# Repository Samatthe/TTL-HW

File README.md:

# TTL-HW
Hardware for the TelTail Light's Control Module, an interactive lighting controller for DIY electric skateboards

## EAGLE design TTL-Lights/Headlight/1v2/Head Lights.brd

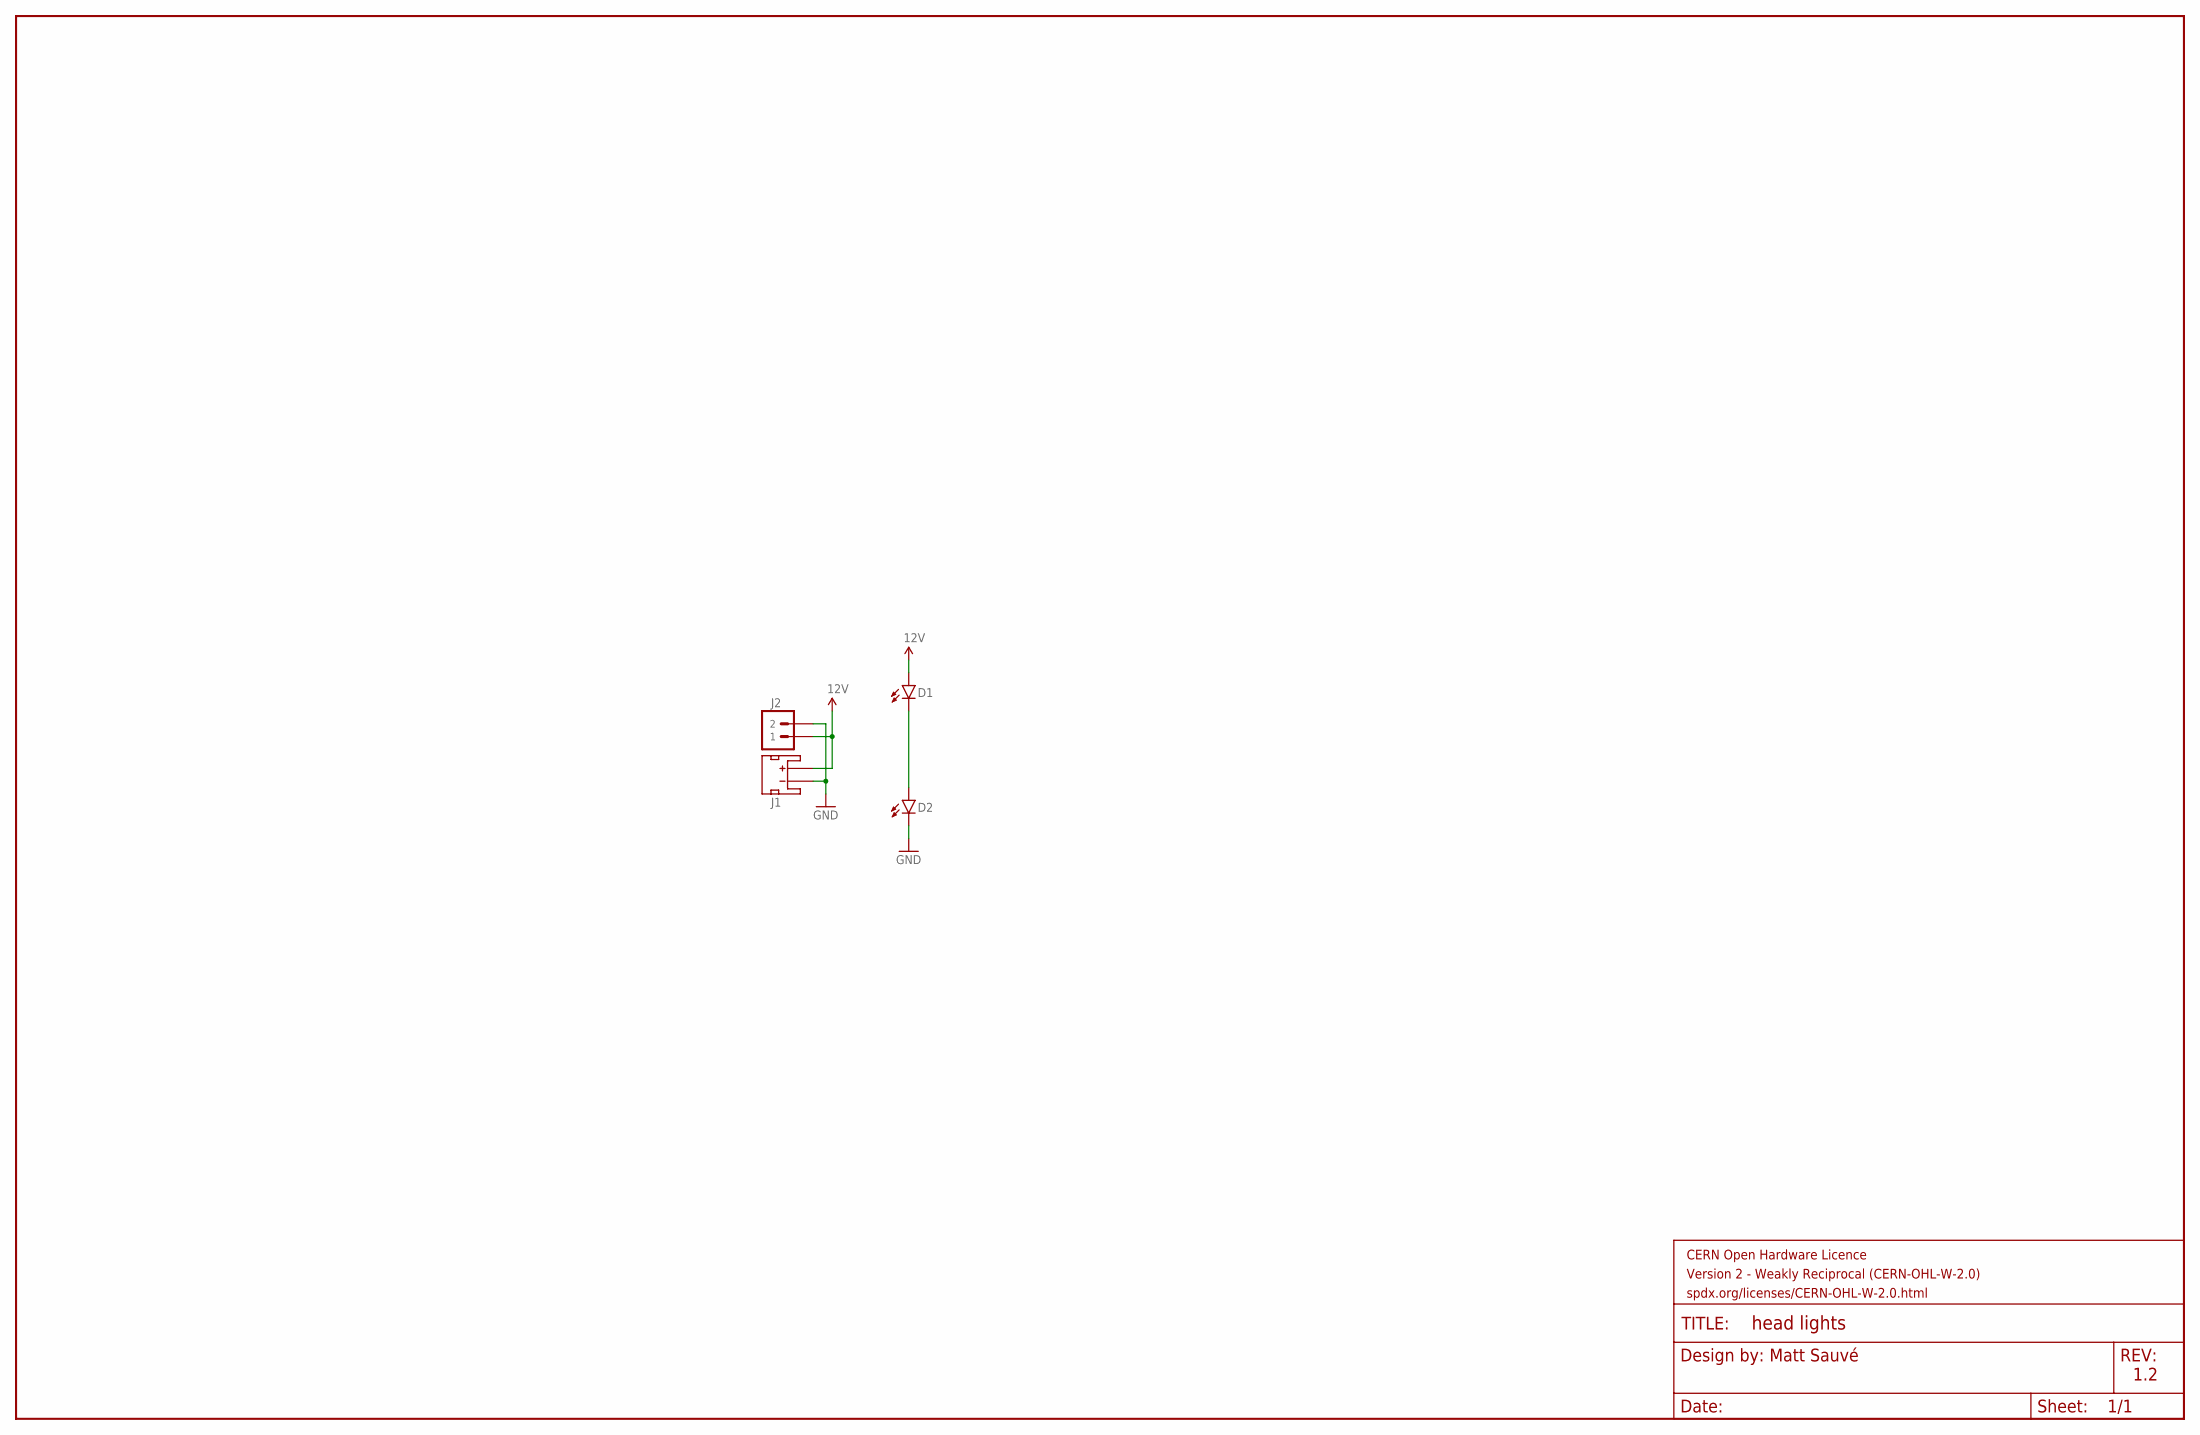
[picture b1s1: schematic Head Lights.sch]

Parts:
D1, D2: WHITE_LUXEON_LED; 1414
FRAME1: FRAME-LEDGER_CERN_WEAK; CERN_WEAK
J1: JST_2MM_MALE; JST-2-SMD
J2: JST_PH_2POS

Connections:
12V: D1.P$1 (A), J1.2 (+), J2.1
GND: D2.P$2 (C), J1.1 (-), J2.2
unnamed: D1.P$2 (C), D2.P$1 (A)

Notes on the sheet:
Matt Sauvé
1.2

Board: 2 copper layers, 5 parts (2 on the bottom side), 3 nets, no tracks yet.

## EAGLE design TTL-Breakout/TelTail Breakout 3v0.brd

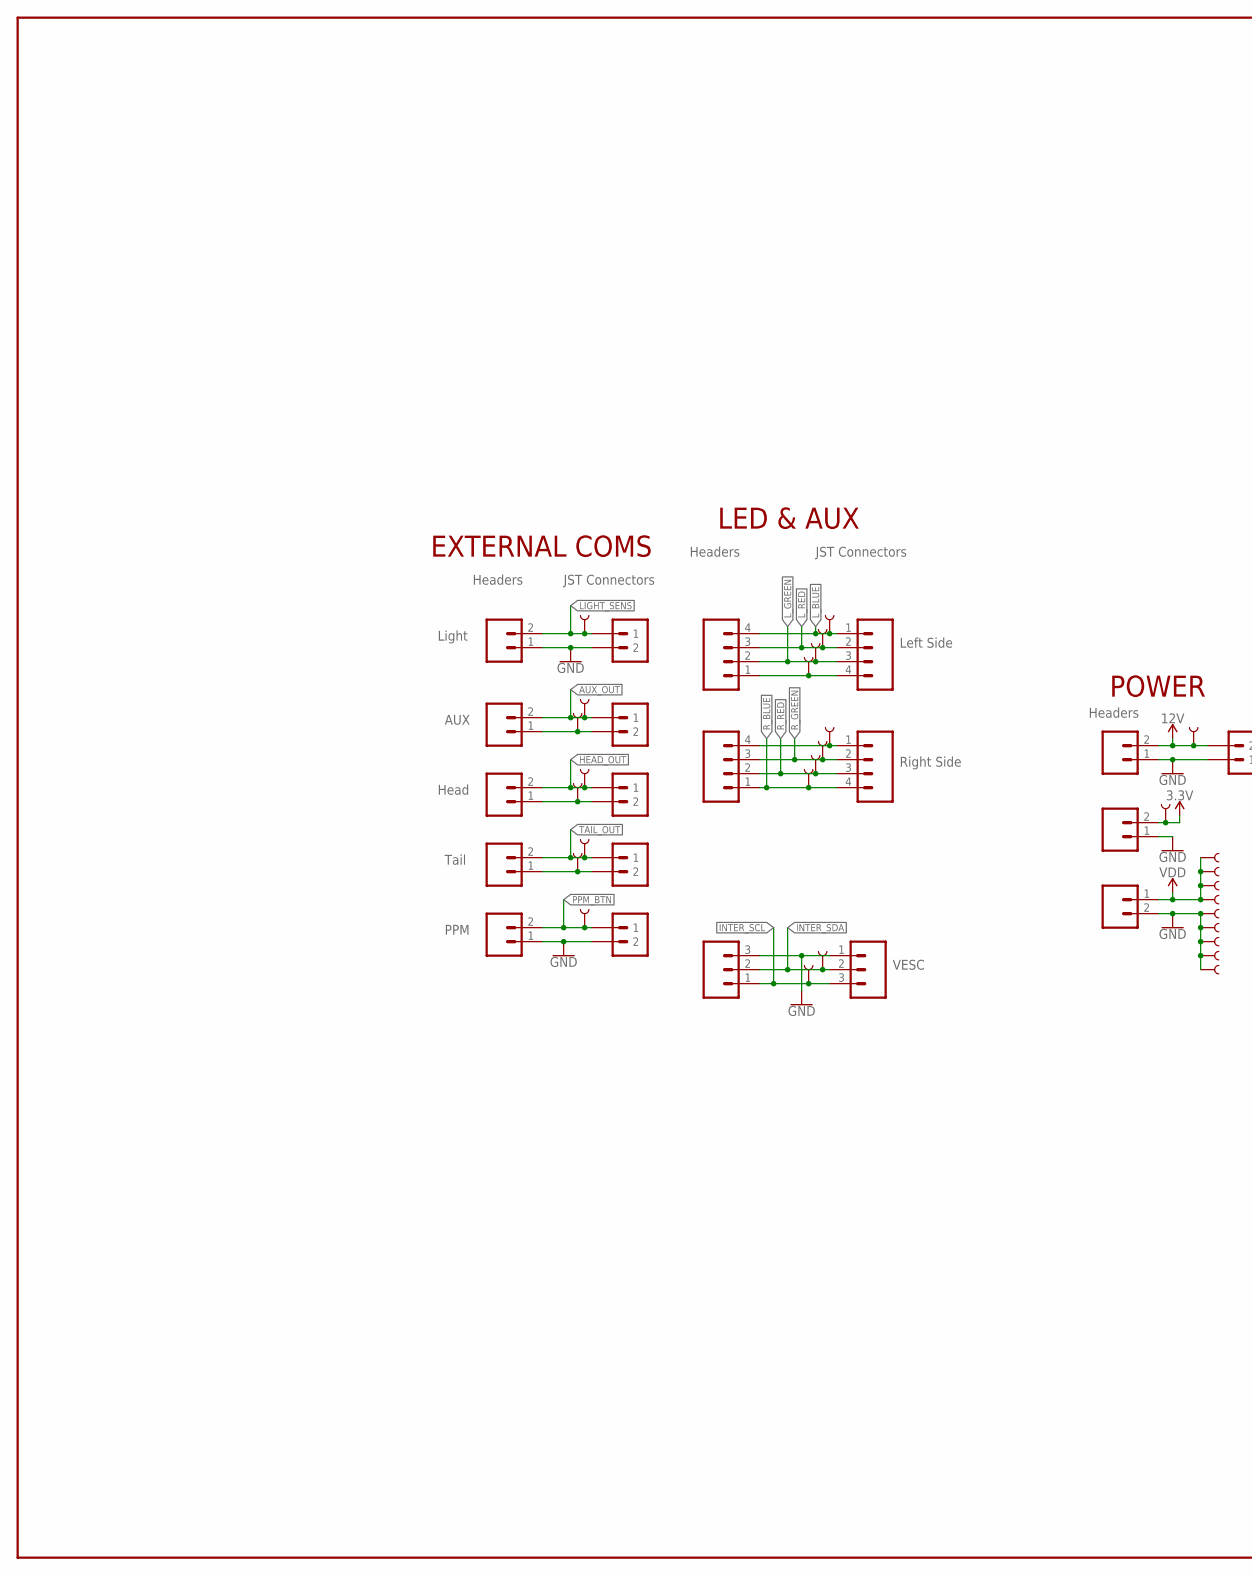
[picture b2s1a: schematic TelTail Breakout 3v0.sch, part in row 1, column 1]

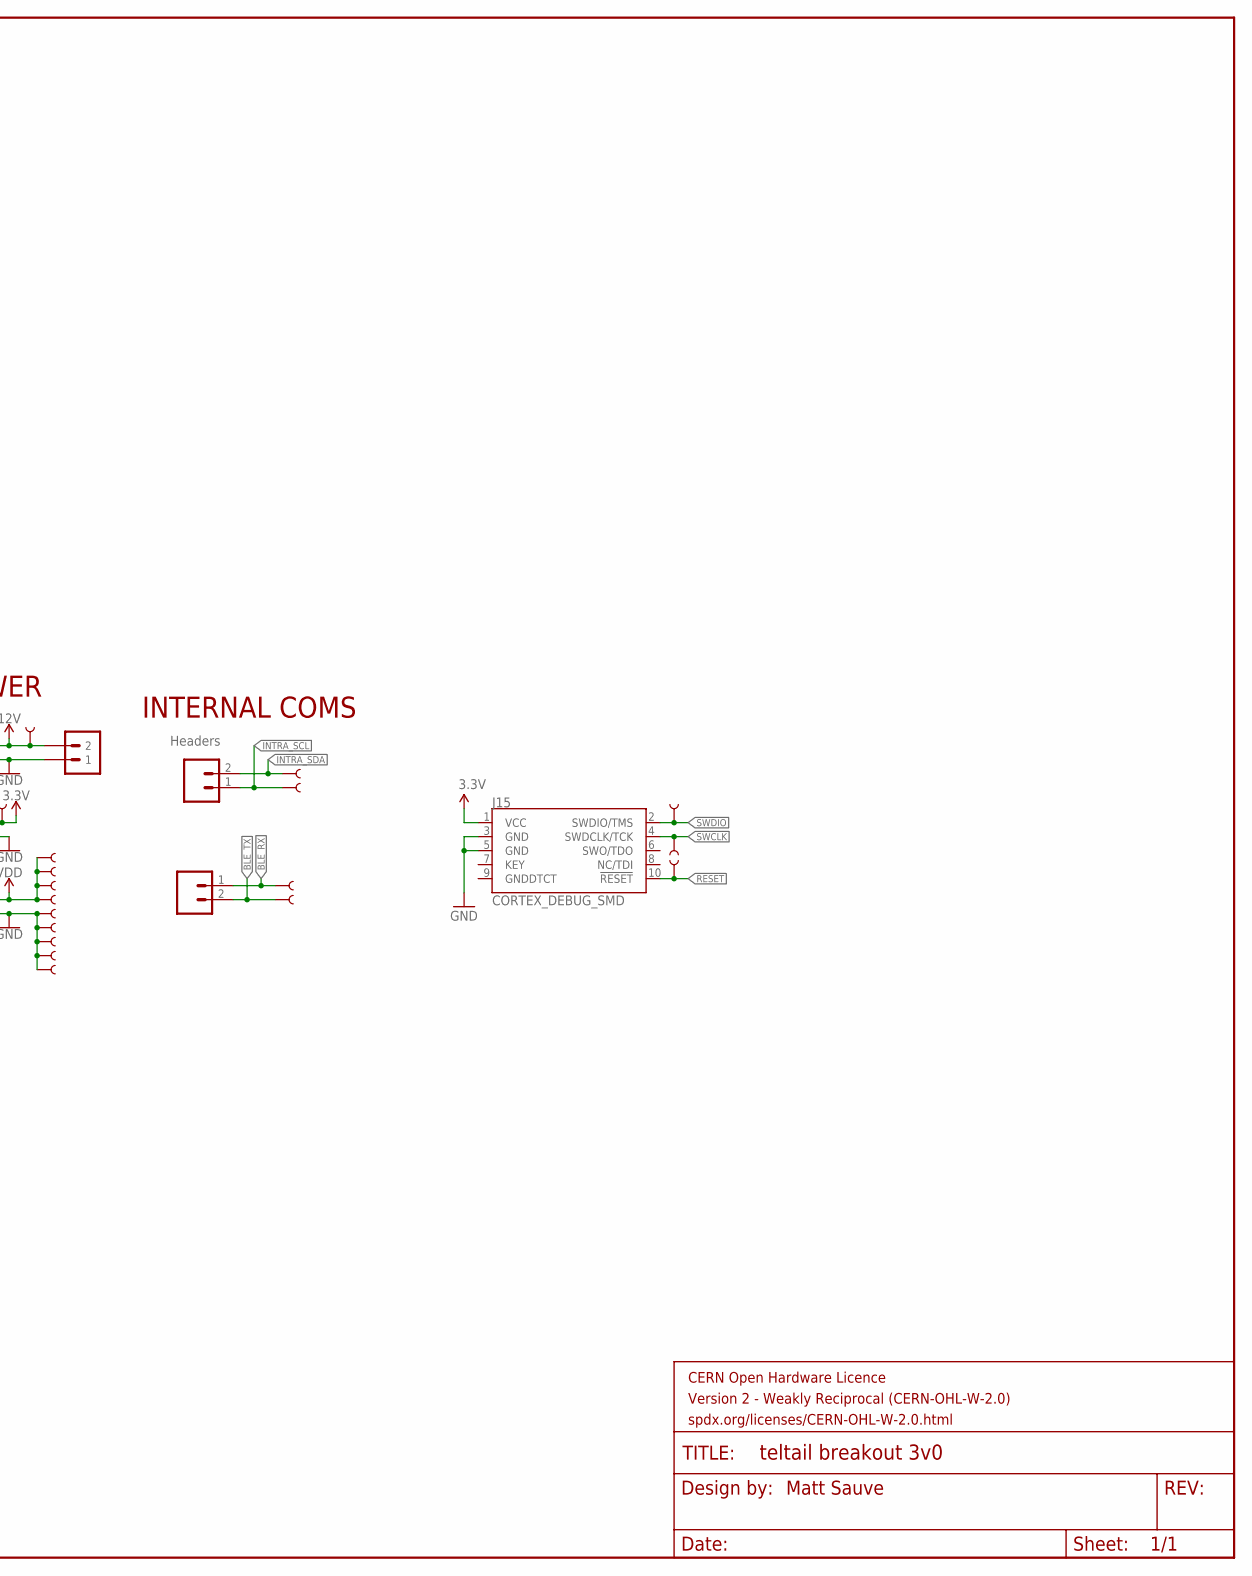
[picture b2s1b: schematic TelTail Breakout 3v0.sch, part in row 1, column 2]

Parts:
FRAME1: FRAME-LEDGER_CERN_WEAK; CERN_WEAK
J1, J2, J3, J4, J5, J6, J11, J12, J13, J14: CONN_02; 1X02
J7: CONN_03; 1X03
J9, J10: CONN_04; 1X04
J15: CORTEX_DEBUG_SMD; SAMTECH_FTSH-105-01
U$1, U$2, U$3, U$4, U$5, U$45: JST_PH_2POS
U$6, U$11, U$12, U$13, U$14, U$15, U$16, U$17, U$18, U$19, U$20, U$21, U$22, U$23, U$24, U$25, U$26, U$27, U$28, U$29, U$30, U$31, U$32, U$33, U$34, U$35, U$36, U$37, U$38, U$39, U$40, U$42, U$43, U$44, U$46, U$48: POGO_PIN_90173-AS
U$8, U$10: JST_PH_4POS
U$9: JST_PH_3POS

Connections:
3.3V: J12.2, J15.1 (VCC), U$20.P$1
12V: J11.2, U$38.P$1, U$45.2
!RESET: J15.10 (!RESET), U$36.P$1
AUX_OUT: J2.2, U$4.1, U$31.P$1
BLE_RX: J14.1, U$46.P$1
BLE_TX: J14.2, U$48.P$1
GND: J1.1, J5.1, J6.2, J7.3, J11.1, J12.1, J15.3 (GND), J15.5 (GND), U$1.2, U$5.2, U$6.P$1, U$9.1 (2), U$24.P$1, U$28.P$1, U$30.P$1, U$40.P$1, U$45.1
HEAD_OUT: J3.2, U$3.1, U$29.P$1
INTER_SCL: J7.1, U$9.3 (4), U$19.P$1
INTER_SDA: J7.2, U$9.2 (3), U$21.P$1
INTRA_SCL: J13.1, U$44.P$1
INTRA_SDA: J13.2, U$43.P$1
LIGHT_SENS: J1.2, U$5.1, U$33.P$1
L_BLUE: J10.4, U$10.1, U$11.P$1
L_GREEN: J10.2, U$10.3, U$13.P$1
L_RED: J10.3, U$10.2, U$12.P$1
unnamed: J4.1, U$2.2, U$35.P$1
unnamed: J3.1, U$3.2, U$34.P$1
unnamed: J2.1, U$4.2, U$32.P$1
unnamed: J10.1, U$10.4, U$14.P$1
unnamed: J9.4, U$8.1, U$15.P$1
PPM_BTN: J5.2, U$1.1, U$25.P$1
R_BLUE: J9.1, U$8.4, U$18.P$1
R_GREEN: J9.3, U$8.2, U$16.P$1
R_RED: J9.2, U$8.3, U$17.P$1
SWCLK: J15.4 (SWDCLK/TCK), U$37.P$1
SWDIO: J15.2 (SWDIO/TMS), U$39.P$1
TAIL_OUT: J4.2, U$2.1, U$27.P$1
VDD: J6.1, U$22.P$1, U$23.P$1, U$26.P$1, U$42.P$1

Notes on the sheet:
VESC
Right Side
Left Side
JST Connectors
Headers
Light
AUX
Head
Tail
PPM
POWER
LED & AUX
EXTERNAL COMS
INTERNAL COMS
Matt Sauve

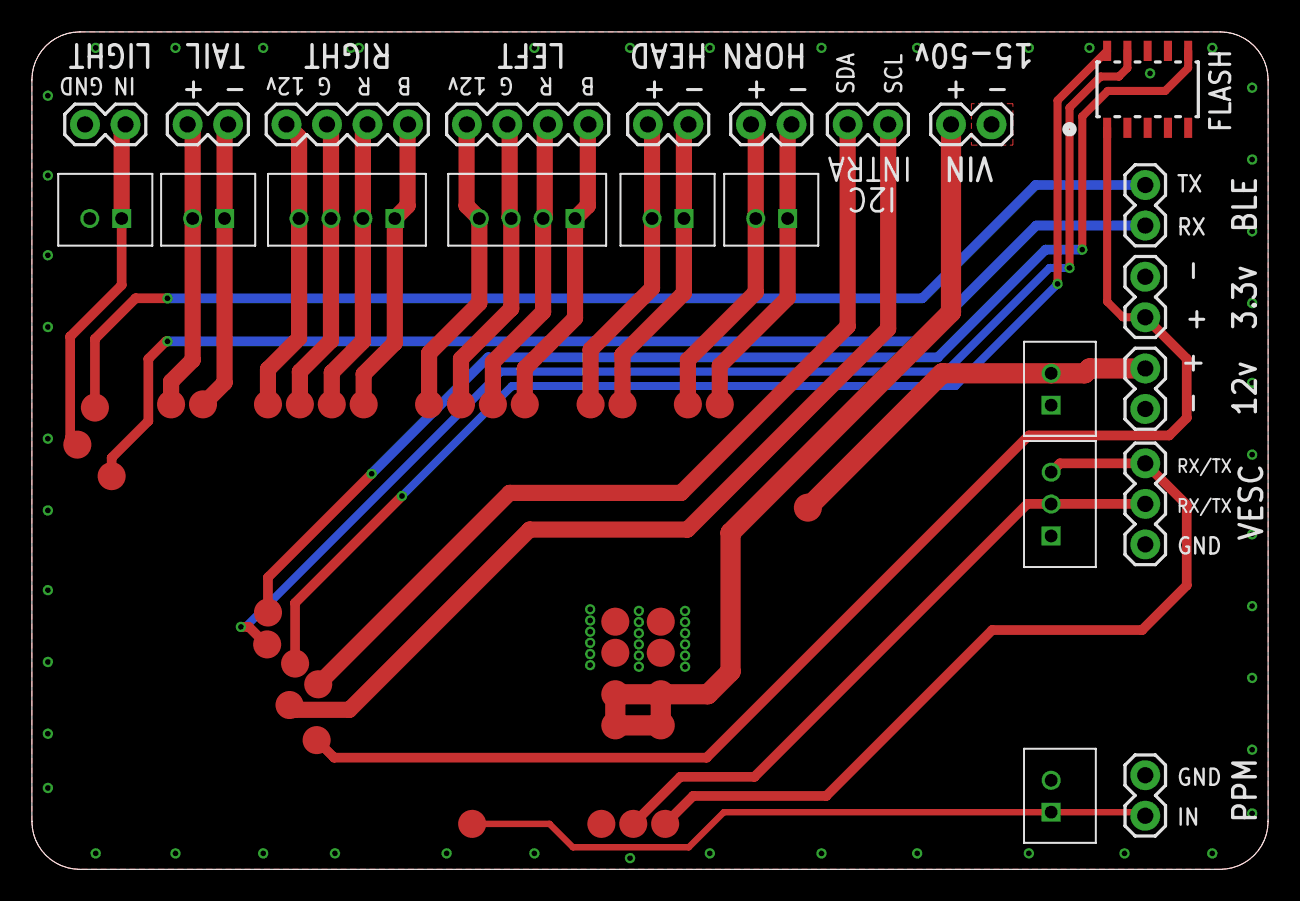
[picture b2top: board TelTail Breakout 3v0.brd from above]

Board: 2 copper layers, 77.5 x 52.5 mm, 61 parts (1 on the bottom side), 29 nets.

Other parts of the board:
U$41: TTL_LARGE

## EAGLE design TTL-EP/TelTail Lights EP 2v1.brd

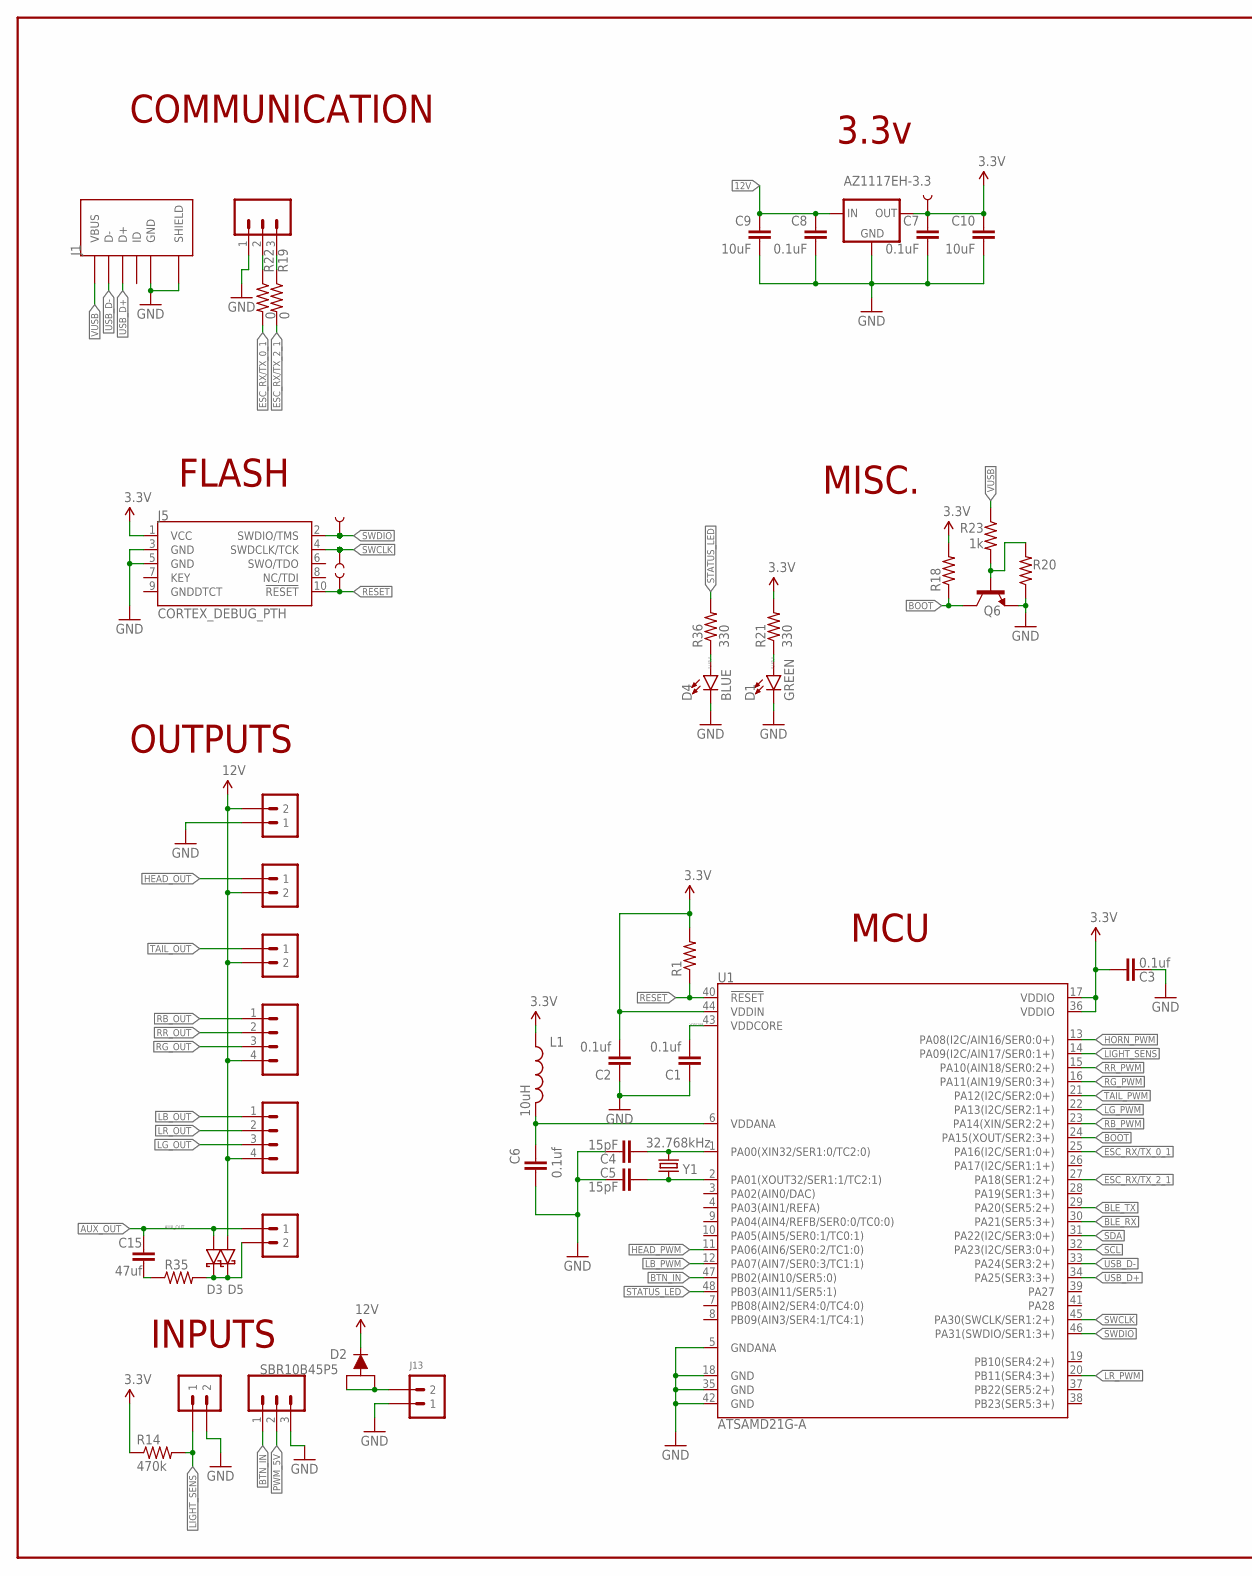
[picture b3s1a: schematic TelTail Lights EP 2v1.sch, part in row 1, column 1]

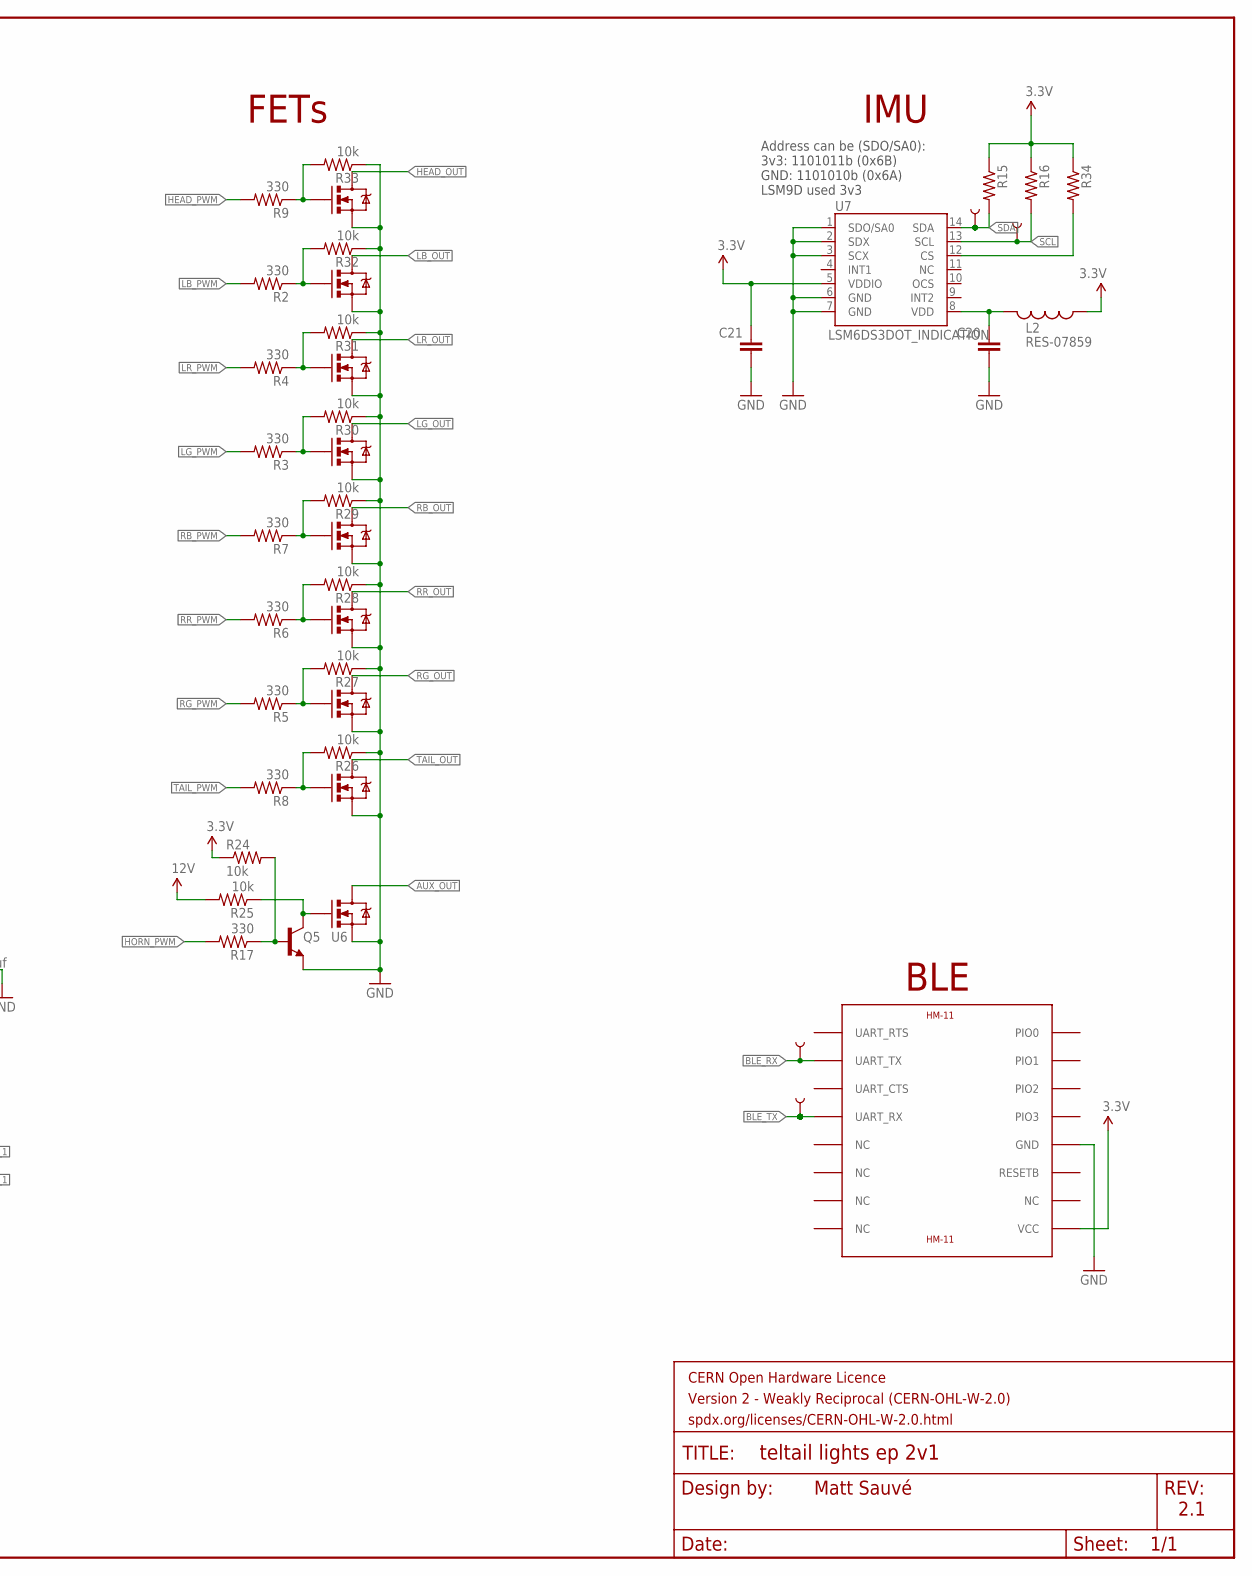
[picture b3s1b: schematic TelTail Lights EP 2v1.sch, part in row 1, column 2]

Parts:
C1, C2, C3, C6: 0.1uf; 0603-CAP
C4, C5: 15pF; 0603-CAP
C7, C8, C20, C21: 0.1uF; 0603-CAP
C9, C10: 10uF; 0603-CAP
C15: 47uf; 1210-CAP
D1: GREEN; LED-0603-2
D2: SBR10B45P5; POWERDI5
D3, D5: PMEG2010ER; SOD-123W
D4: BLUE; LED-0603-2
FRAME1: FRAME-LEDGER_CERN_WEAK; CERN_WEAK
J1: USB3160-XX-XXXX-X-X_REVA; GCT_USB3160-XX-XXXX-X-X_REVA
J3, J12: JST_PH_3POS
J4, J6, J7, J10, J11: JST_PH_2POS
J5: CORTEX_DEBUG_PTH; 2X5-PTH-1.27MM-2
J8, J9: JST_PH_4POS
J13: TERM_BLOCK_SPRING_2POS_5MM
L1: 10uH; 0603-IND
L2: RES-07859; 0603-IND
Q1, Q2, Q3, Q4: DUAL_NFET_3.5A; TSOT26
Q5, Q6: 500mA/300V; SOT23-3
R1, R15, R16, R18, R20, R24, R25, R26, R27, R28, R29, R30, R31, R32, R33, R34: 10k; RES-0402
R2, R3, R4, R5, R6, R7, R8, R9, R17, R21, R36: 330; RES-0402
R14: 470k; RES-0603
R19, R22: 0; RES-0603
R23: 1k; RES-0402
R35: 100; 0805-RES
TP1, TP2, TP3, TP4, TP5, TP8, TP9, TP10: 1MM_TP
U1: ATSAMD21G-A; TQFP-48
U3: HM-11
U4: AZ1117EH-3.3; SOT-223
U6: PSMN8R5-60YS; SOT669
U7: LSM6DS3DOT_INDICATION; LGA14L_DOT_INDICATOR
Y1: 32.768kHz; CRYSTAL-SMD-3.2X1.5MM

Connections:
3.3V: C2.2, C3.2, C7.1, C10.1, C21.1, J5.1 (VCC), L1.1, L2.1, R1.2, R14.1, R15.1, R16.1, R18.2, R21.2, R24.1, R34.1, TP3.P$1, U1.17 (VDDIO), U1.36 (VDDIO), U1.44 (VDDIN), U3.VCC, U4.2 (OUT), U4.4 (OUT), U7.5 (VDDIO)
12V: C8.1, C9.1, D2.CATHODE (C), D5.2 (ANODE), J4.2, J6.2, J7.2, J8.4, J9.4, R25.2, U4.3 (IN)
!RESET: J5.10 (!RESET), R1.1, TP10.P$1, U1.40 (!RESET!)
AUX_OUT: C15.1, D3.2 (ANODE), J10.1, U6.P$1 (D), U6.P$2 (D)
BLE_RX: TP2.P$1, U1.30 (PA21(SER5:3+)), U3.UART_TX
BLE_TX: TP1.P$1, U1.29 (PA20(SER5:2+)), U3.UART_RX
BOOT: Q6.3 (C), R18.1, U1.24 (PA15(XOUT/SER2:3+))
BTN_IN: J12.1 (2), U1.47 (PB02(AIN10/SER5:0))
ESC_RX/TX_0_0: J3.2 (3), R22.1
ESC_RX/TX_0_1: R22.2, U1.25 (PA16(I2C/SER1:0+))
ESC_RX/TX_2_0: J3.3 (4), R19.1
ESC_RX/TX_2_1: R19.2, U1.27 (PA18(SER1:2+))
GND: C1.1, C2.1, C3.1, C4.2, C5.2, C6.2, C7.2, C8.2, C9.2, C10.2, C20.2, C21.2, D1.C, D4.C, J1.5 (GND), J1.6 (SHIELD), J1.7 (SHIELD), J1.8 (SHIELD), J3.1 (2), J4.1, J5.3 (GND), J5.5 (GND), J11.2, J12.3 (4), J13.P1_1 (1), J13.P1_2 (1), Q1.2 (S), Q1.5 (S), Q2.2 (S), Q2.5 (S), Q3.2 (S), Q3.5 (S), Q4.2 (S), Q4.5 (S), Q5.2 (E), Q6.2 (E), R20.1, R26.1, R27.1, R28.1, R29.1, R30.1, R31.1, R32.1, R33.1, U1.5 (GNDANA), U1.18 (GND), U1.35 (GND), U1.42 (GND), U3.GND, U4.1 (GND), U6.1 (S), U6.2 (S), U6.3 (S), U7.1 (SDO/SA0), U7.2 (SDX), U7.3 (SCX), U7.6 (GND), U7.7 (GND)
HEAD_OUT: J6.1, Q1.4 (D)
HEAD_PWM: R9.2, U1.11 (PA06(AIN6/SER0:2/TC1:0))
HORN_PWM: R17.2, U1.13 (PA08(I2C/AIN16/SER0:0+))
IMU_CS: R34.2, U7.12 (CS)
LB_OUT: J9.1, Q1.6 (D)
LB_PWM: R2.2, U1.12 (PA07(AIN7/SER0:3/TC1:1))
LG_OUT: J9.3, Q2.6 (D)
LG_PWM: R3.2, U1.22 (PA13(I2C/SER2:1+))
LIGHT_SENS: J11.1, R14.2, U1.14 (PA09(I2C/AIN17/SER0:1+))
LR_OUT: J9.2, Q2.4 (D)
LR_PWM: R4.2, U1.20 (PB11(SER4:3+))
unnamed: Q1.1 (G), R2.1, R32.2
unnamed: Q1.3 (G), R9.1, R33.2
unnamed: D3.1 (CATHODE), D5.1 (CATHODE), J10.2, R35.2
unnamed: C6.1, L1.2, U1.6 (VDDANA)
unnamed: Q2.3 (G), R4.1, R31.2
unnamed: Q2.1 (G), R3.1, R30.2
unnamed: Q3.3 (G), R7.1, R29.2
unnamed: Q3.1 (G), R6.1, R28.2
unnamed: Q4.3 (G), R5.1, R27.2
unnamed: Q4.1 (G), R8.1, R26.2
unnamed: Q5.1 (B), R17.1, R24.2
unnamed: Q6.1 (B), R20.2, R23.2
unnamed: C15.2, R35.1
unnamed: Q5.3 (C), R25.1, U6.4 (G)
unnamed: C5.1, U1.2 (PA01(XOUT32/SER1:1/TC2:1)), Y1.P$1 (1)
PWM_5V: J12.2 (3)
P_LED_0: D1.A, R21.1
RB_OUT: J8.1, Q3.4 (D)
RB_PWM: R7.2, U1.23 (PA14(XIN/SER2:2+))
RG_OUT: J8.3, Q4.4 (D)
RG_PWM: R5.2, U1.16 (PA11(AIN19/SER0:3+))
RR_OUT: J8.2, Q3.6 (D)
RR_PWM: R6.2, U1.15 (PA10(AIN18/SER0:2+))
SCL: R16.2, TP5.P$1, U1.32 (PA23(I2C/SER3:0+)), U7.13 (SCL)
SDA: R15.2, TP4.P$1, U1.31 (PA22(I2C/SER3:0+)), U7.14 (SDA)
STATUS_LED: R36.2, U1.48 (PB03(AIN11/SER5:1))
SWCLK: J5.4 (SWDCLK/TCK), TP9.P$1, U1.45 (PA30(SWCLK/SER1:2+))
SWDIO: J5.2 (SWDIO/TMS), TP8.P$1, U1.46 (PA31(SWDIO/SER1:3+))
S_LED_0: D4.A, R36.1
TAIL_OUT: J7.1, Q4.6 (D)
TAIL_PWM: R8.2, U1.21 (PA12(I2C/SER2:0+))
USB_D+: J1.3 (D+), U1.34 (PA25(SER3:3+))
USB_D-: J1.2 (D-), U1.33 (PA24(SER3:2+))
VCC: D2.ANODE1 (A), D2.ANODE2 (A1), J13.P2_1 (2), J13.P2_2 (2)
VDD: C20.1, L2.2, U7.8 (VDD)
VDDANA: C4.1, U1.1 (PA00(XIN32/SER1:0/TC2:0)), Y1.P$2 (2)
VDDCORE: C1.2, U1.43 (VDDCORE)
VUSB: J1.1 (VBUS), R23.1

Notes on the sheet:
COMMUNICATION
INPUTS
IMU
OUTPUTS
3.3v
BLE
MISC.
FETs
MCU
FLASH
Matt Sauvé
2.1
Address can be (SDO/SA0): 3v3: 1101011b (0x6B) GND: 1101010b (0x6A) LSM9D used 3v3

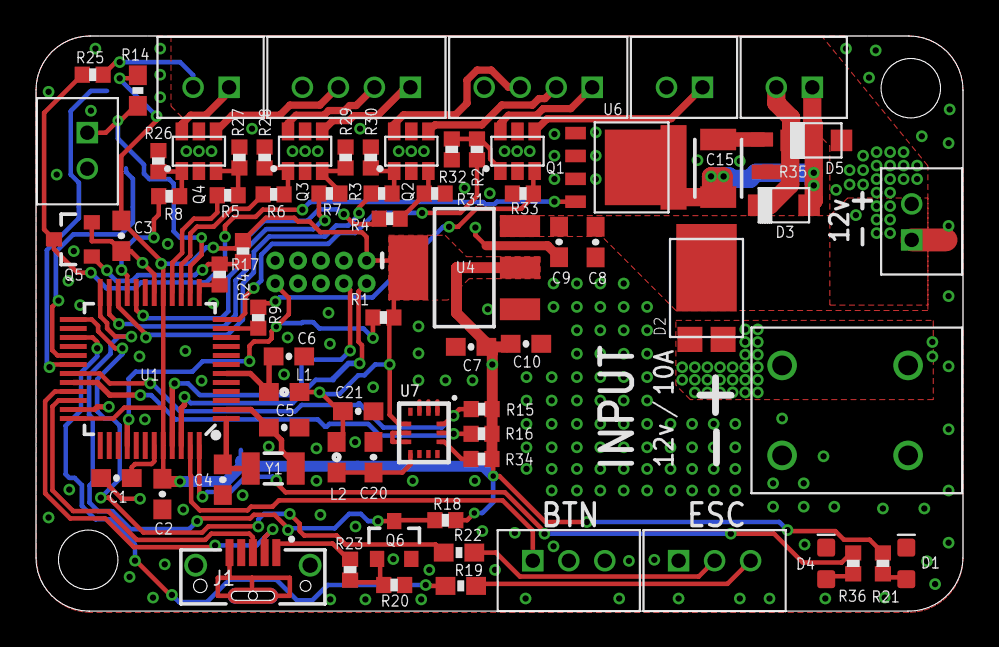
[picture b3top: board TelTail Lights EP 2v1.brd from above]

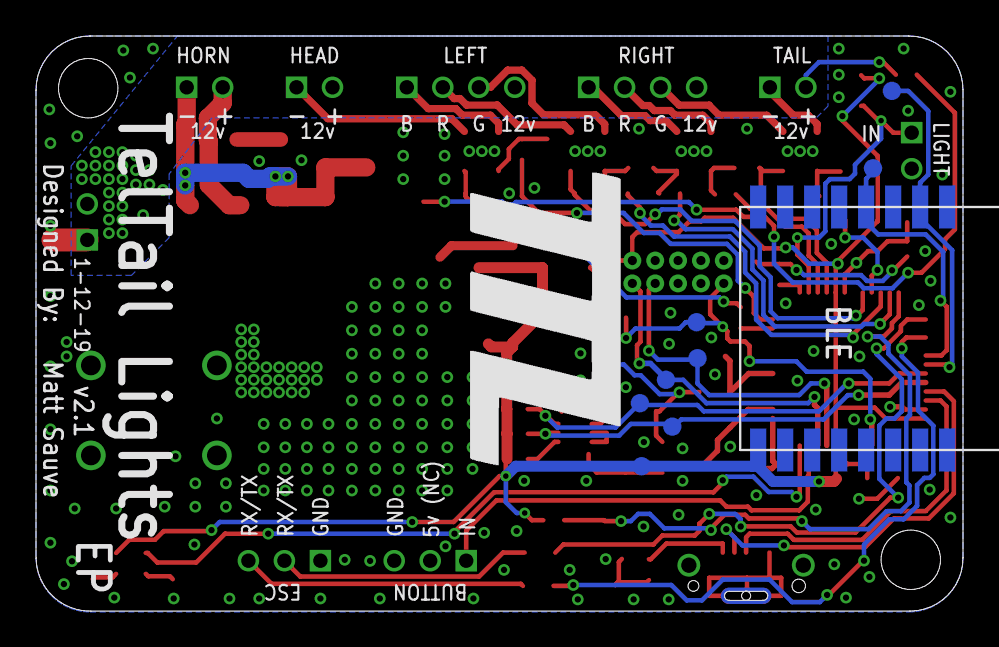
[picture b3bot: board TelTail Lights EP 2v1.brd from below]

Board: 2 copper layers, 51.5 x 31.9 mm, 88 parts (10 on the bottom side), 61 nets.

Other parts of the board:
U$4, U$5: STAND-OFF
U$22: TTL_LARGE

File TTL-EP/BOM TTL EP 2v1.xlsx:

# | Manufacturer Part# | Manufacturer | Value | Package | Designator | Quantity | Link | Note
1 | RMCF0603ZT0R00 | Stackpole Electronics Inc | 0 | 0603 | R19, R22 | 2 | https://www.digikey.com/product-detail/en/stackpole-electron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
2 | CS0603KRX7R7BB104 | Yageo | 0.1uf | 0603 | C1, C2, C3, C6, C7, C8, C20, C21 | 8 | https://www.digikey.com/product-detail/en/stackpole-electron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
3 | ERJ-P06J101V | Panasonic Electronic Components | 100 | 0805 | R35 | 1 | https://www.digikey.com/product-detail/en/panasonic-electron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
4 | RMCF0402JT10K0 | Stackpole Electronics Inc | 10k | 0402 | R1, R15, R16, R18, R20, R24, R25, R26, R27, R28, R29, R30, R31, R32, R33, R34 | 16 | https://www.digikey.com/product-detail/en/stackpole-electron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
5 | CL10X106MO8NRNC | Samsung Electro-Mechanics | 10uF, 16v | 0603 | C9 | 1 | https://www.digikey.com/product-detail/en/samsung-electro-me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
6 | CL10A106MA8NRNC | Samsung Electro-Mechanics | 10uF, 25v | 0603 | C10 | 1 | https://www.digikey.com/product-detail/en/samsung-electro-me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
7 | AIML-0603-100K-T | Abracon LLC | 10uH | 0603 | L1 | 1 | https://www.digikey.com/product-detail/en/abracon-llc/AIML-0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
8 | C1608C0G2A150J080AA | TDK Corporation | 15pf | 0603 | C4, C5 | 2 | https://www.digikey.com/product-detail/en/tdk-corporation/C1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
9 | RMCF0402JT1K00 | Stackpole Electronics Inc | 1k | 0402 | R23 | 1 | https://www.digikey.com/product-detail/en/stackpole-electron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
10 | ABS07-32.768KHZ-T | Abracon LLC | 32.768kHz | SMD-3.2X1.5MM | Y1 | 1 | https://www.digikey.com/product-detail/en/abracon-llc/ABS07-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
11 | RMCF0402JT330R | Stackpole Electronics Inc | 330 | 0402 | R2, R3, R4, R5, R6, R7, R8, R9, R17, R21, R36 | 11 | https://www.digikey.com/product-detail/en/stackpole-electron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
12 | RMCF0603JT470K | Stackpole Electronics Inc. | 470k | 0603 | R14 | 1 | https://www.digikey.com/product-detail/en/stackpole-electron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
13 | GRM32EC81C476KE15K | Murata Electronics | 47uf | 1210 | C15 | 3 | https://www.digikey.com/product-detail/en/murata-electronics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
14 | BC846B RFG | Taiwan Semiconductor Corporation | N/A | SOT23-3 | Q5, Q6 | 2 | https://www.digikey.com/product-detail/en/taiwan-semiconduct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
15 | ATSAMD21G18A-AUT | Microchip Technology | N/A | 48-TQFP | U1 | 1 | https://www.digikey.com/product-detail/en/microchip-technolo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
16 | AZ1117EH-3.3TRG1 | Diodes Incorporated | AZ1117EH-3.3 | SOT-223 | U4 | 1 | https://www.digikey.com/product-detail/en/diodes-incorporate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
17 | 150060BS55040 | Wurth Electronics Inc. | Blue | 0603 | D4 | 1 | https://www.digikey.com/product-detail/en/wurth-electronics-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
18 | DMN3135LVT-7 | Diodes Incorporated | 3.5A | TSOT26 | Q1, Q2, Q3, Q4 | 4 | https://www.digikey.com/product-detail/en/diodes-incorporate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
19 | 150060VS55040 | Wurth Electronics Inc. | Green | 0603 | D1 | 1 | https://www.digikey.com/product-detail/en/wurth-electronics-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
20 | LSM6DSMTR | STMicroelectronics | N/A | 14-VFLGA | U7 | 1 | https://www.digikey.com/product-detail/en/stmicroelectronics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
21 | PMEG6020ER,115 | Nexperia USA Inc. | .5v, 2A | SOD-123W | D3, D5 | 2 | https://www.digikey.com/product-detail/en/nexperia-usa-inc/P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,115/1727-…
22 | PSMN012-60YS,115 | Nexperia USA Inc. | 60v, 59A | LFPAK56, Power-SO8 | U6 | 1 | https://www.digikey.com/product-detail/en/nexperia-usa-inc/P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,115/172…
23 | MPZ1608D300BTD25 | TDK Corporation | 30 Ohms @ 100MHz | 0603 | L2 | 1 | https://www.digikey.com/product-detail/en/tdk-corporation/MP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
24 | SS215-HF | Comchip Technology | 100v, 2A | DO-214AC, SMA | D2 | 1 | https://www.digikey.com/product-detail/en/comchip-technology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
25 | USB3160-30-0170-1-C | GCT | N/A | N/A | J1 | 1 | https://www.digikey.com/product-detail/en/gct/USB3160-30-017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

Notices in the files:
parts and their libraries:
SAUVE: Released under the CERN Open Hardware Licence Version 2 - Weakly Reciprocal (CERN-OHL-W-2.0)
SAUVE: spdx.org/licenses/CERN-OHL-W-2.0.html
SparkFun-Connectors: Licensing: Creative Commons ShareAlike 4.0 International - https://creativecommons.org/licenses/by-sa/4.0
